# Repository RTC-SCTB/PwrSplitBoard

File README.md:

# PwrSplitBoard
Плата раздачи питания.  
Для подключения используются клеммники MKDSN 1.5/2-5.08

## Содержание
- Gerber файлы - в папке `Gerbers`

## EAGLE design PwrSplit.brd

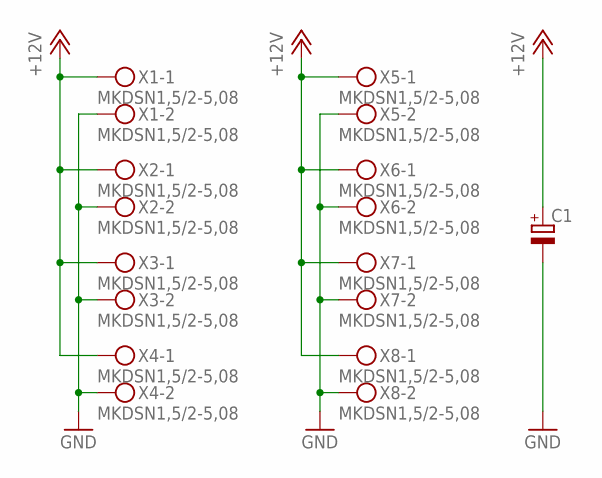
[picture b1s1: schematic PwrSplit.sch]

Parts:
C1: ECAP; E5-13
X1, X2, X3, X4, X5, X6, X7, X8: MKDSN1,5/2-5,08

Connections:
+12V: C1.+, X1.1, X2.1, X3.1, X4.1, X5.1, X6.1, X7.1, X8.1
GND: C1.-, X1.2, X2.2, X3.2, X4.2, X5.2, X6.2, X7.2, X8.2

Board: 2 copper layers, 10 parts (0 on the bottom side), 2 nets, no tracks yet.

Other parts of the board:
U$1: MASKLABEL

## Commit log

2018-10-24 Firs commit
2018-10-24 Добавлен Readme, переименована папка Gerbers, удалены ненужные файлы.
